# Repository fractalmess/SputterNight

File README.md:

# SputterNight
Consolidated efforts towards refurbishing a Edwards 306 sputter tool in oakland Ca

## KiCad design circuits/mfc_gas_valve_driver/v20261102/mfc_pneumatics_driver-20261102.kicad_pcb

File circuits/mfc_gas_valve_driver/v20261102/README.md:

Initial commit version of MFC, front panel and gas valve driver circuit.

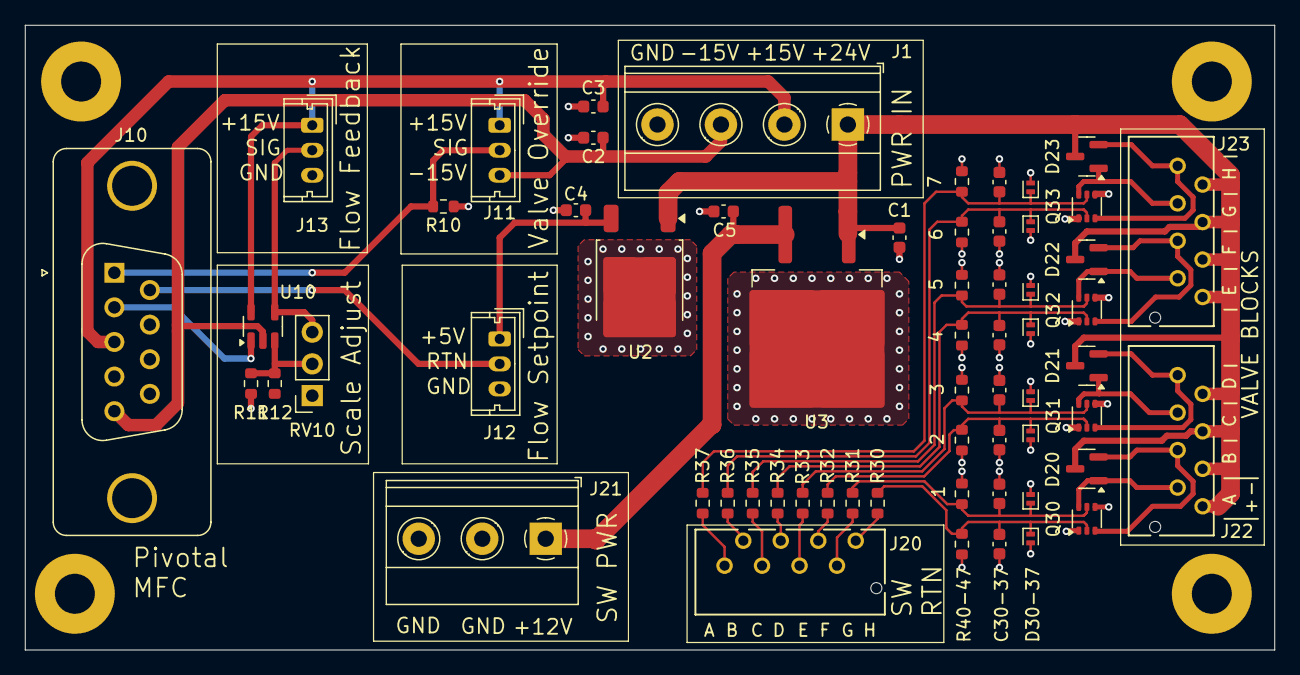
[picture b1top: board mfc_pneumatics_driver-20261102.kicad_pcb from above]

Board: 2 copper layers, 100.0 x 50.0 mm, 65 parts (0 on the bottom side), 36 nets.

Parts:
C1, C2, C3, C4, C5: 1u 50V X7R; C_0603_1608Metric
C30, C31, C32, C33, C34, C35, C36, C37: C; C_0603_1608Metric
D20, D21, D22, D23: BAT54C; SOT-23
D30, D31, D32, D33, D34, D35, D36, D37: DF2S16CT; D_SOD-882
H1, H2, H3, H4: MountingHole_Pad; MountingHole_3.2mm_M3_Pad
J1: Screw_Terminal_01x04; TerminalBlock_Phoenix_MKDS-1,5-4-5.08_1x04_P5.08mm_Horizont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
J10: DE9_Receptacle_MountingHoles; DSUB-9_Female_Vertical_P2.77x2.84mm_MountingHoles
J11, J12, J13: Screw_Terminal_01x03; Molex_Micro-Latch_53253-0370_1x03_P2.00mm_Vertical
J20, J22, J23: Conn_01x08_Socket; Molex_CLIK-Mate_50315908_2x04-1MP_P1.50mm_Vertical
J21: Screw_Terminal_01x03; TerminalBlock_Phoenix_MKDS-1,5-3-5.08_1x03_P5.08mm_Horizont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
Q30, Q31, Q32, Q33: SSM6N7002KFU; SOT-363_SC-70-6
R10, R40, R41, R42, R43, R44, R45, R46, R47: 10k; R_0603_1608Metric
R11: 1k; R_0603_1608Metric
R12: 953R; R_0603_1608Metric
R30, R31, R32, R33, R34, R35, R36, R37: 10R; R_0603_1608Metric
RV10: 100R; PinSocket_1x03_P2.54mm_Vertical
U2: MC78M05_TO252; TO-252-2
U3: MC7812-TO263; TO-263-2
U10: LM321; SOT-23-5

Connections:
+5V: C4.1, J12.1, U2.3 (VO)
+12V: C5.1, J21.1, U3.3 (VO)
+15V: C3.1, J1.2, J10.3, J11.1, J13.1, U10.5 (V+)
+24V: C1.1, D20.3, D21.3, D22.3, D23.3, J1.1, J22.1, J22.3, J22.5, J22.7, J23.1, J23.3, J23.5, J23.7, U2.1 (VI), U3.1 (VI)
-15V: C2.2, J1.3, J10.5, J11.3, U10.2 (V-)
/SW1: J20.1, R30.1
/SW2: J20.2, R31.1
/SW3: J20.3, R32.1
/SW4: J20.4, R33.1
/SW5: J20.5, R34.1
/SW6: J20.6, R35.1
/SW7: J20.7, R36.1
/SW8: J20.8, R37.1
/valve_driver_1/V1_RETURN: D20.1, J22.2, Q30.6 (D)
/valve_driver_1/V2_RETURN: D20.2, J22.4, Q30.3 (D)
/valve_driver_1/V3_RETURN: D21.1, J22.6, Q31.6 (D)
/valve_driver_1/V4_RETURN: D21.2, J22.8, Q31.3 (D)
/valve_driver_2/V1_RETURN: D22.1, J23.2, Q32.6 (D)
/valve_driver_2/V2_RETURN: D22.2, J23.4, Q32.3 (D)
/valve_driver_2/V3_RETURN: D23.1, J23.6, Q33.6 (D)
/valve_driver_2/V4_RETURN: D23.2, J23.8, Q33.3 (D)
GND: C1.2, C2.1, C3.2, C4.2, C5.2, C30.2, C31.2, C32.2, C33.2, C34.2, C35.2, C36.2, C37.2, D30.2 (A), D31.2 (A), D32.2 (A), D33.2 (A), D34.2 (A), D35.2 (A), D36.2 (A), D37.2 (A), J1.4, J10.0 (PAD), J10.4, J10.7, J10.8, J10.9, J12.3, J13.3, J21.2, J21.3, Q30.1 (S), Q30.4 (S), Q31.1 (S), Q31.4 (S), Q32.1 (S), Q32.4 (S), Q33.1 (S), Q33.4 (S), R10.2, R11.1, R40.1, R41.1, R42.1, R43.1, R44.1, R45.1, R46.1, R47.1, U2.2 (GND), U3.2 (GND)
unnamed: C30.1, D30.1 (K), Q30.2 (G), R30.2, R40.2
unnamed: C31.1, D31.1 (K), Q30.5 (G), R31.2, R41.2
unnamed: C32.1, D32.1 (K), Q31.2 (G), R32.2, R42.2
unnamed: C33.1, D33.1 (K), Q31.5 (G), R33.2, R43.2
unnamed: C34.1, D34.1 (K), Q32.2 (G), R34.2, R44.2
unnamed: C35.1, D35.1 (K), Q32.5 (G), R35.2, R45.2
unnamed: C36.1, D36.1 (K), Q33.2 (G), R36.2, R46.2
unnamed: C37.1, D37.1 (K), Q33.5 (G), R37.2, R47.2
unnamed: J10.1, J11.2, R10.1
unnamed: J10.6, J12.2
unnamed: J13.2, RV10.3, U10.4
unnamed: R12.2, RV10.2
unnamed: J10.2, U10.1 (+)
unnamed: R11.2, R12.1, U10.3 (-)
